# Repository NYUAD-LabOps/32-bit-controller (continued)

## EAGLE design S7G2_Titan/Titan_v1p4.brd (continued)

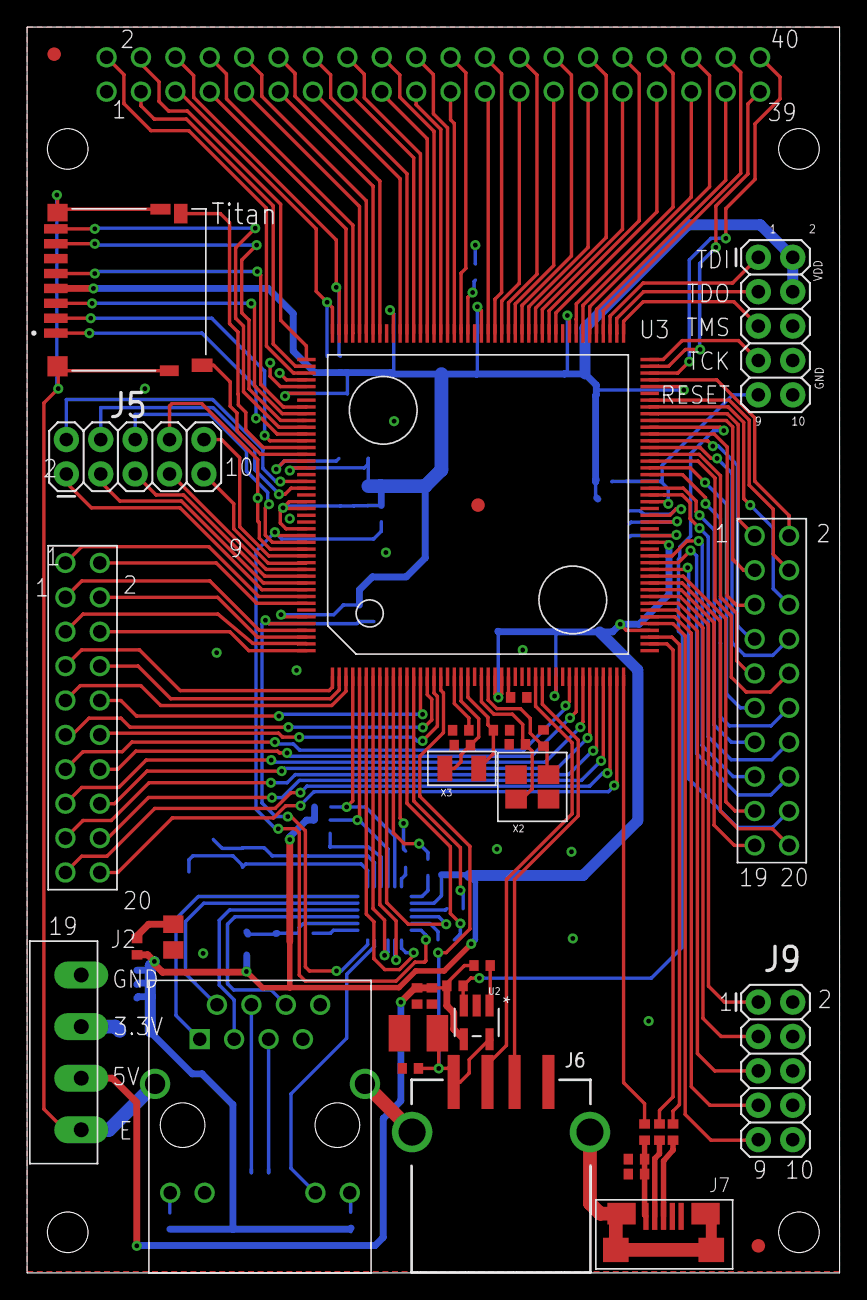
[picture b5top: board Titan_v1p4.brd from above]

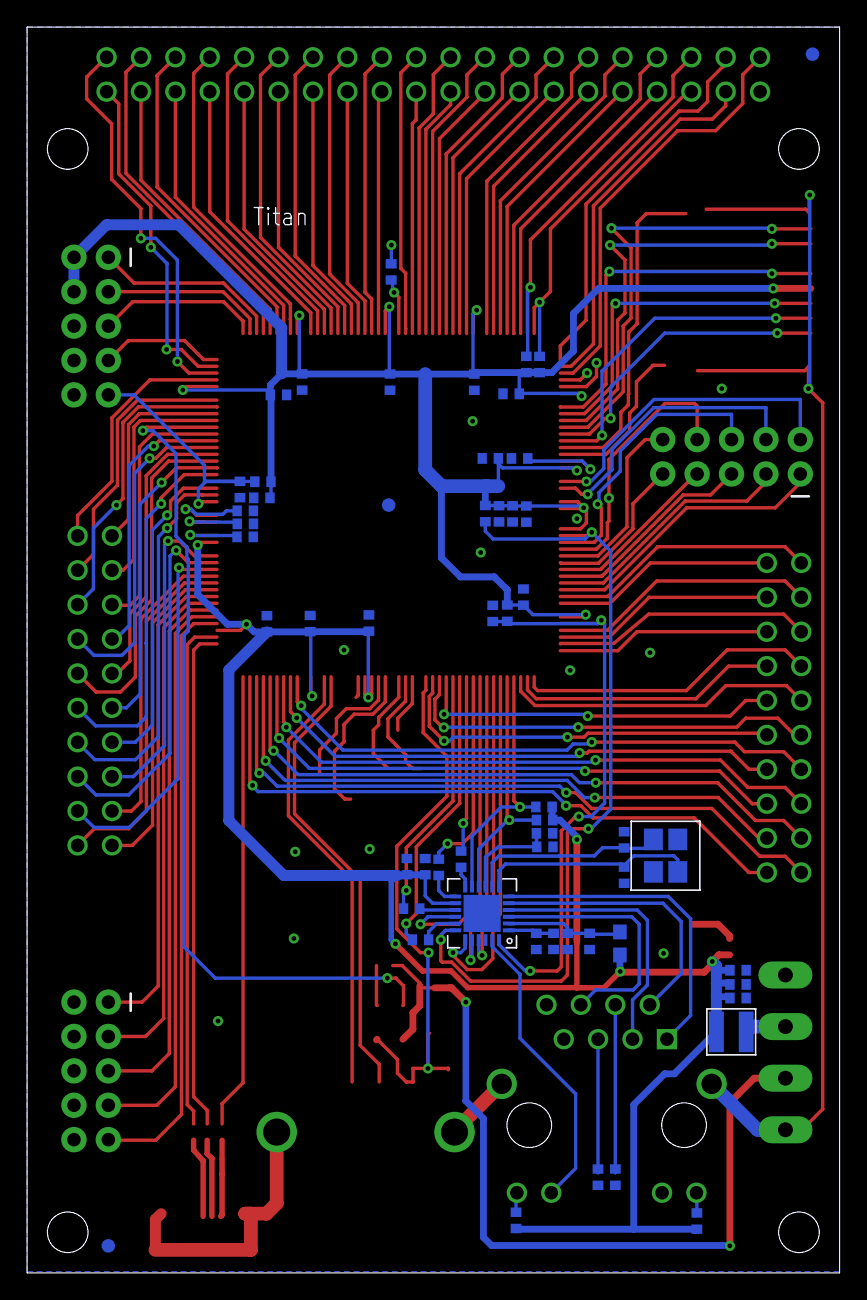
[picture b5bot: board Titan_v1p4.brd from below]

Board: 2 copper layers, 60.0 x 92.0 mm, 93 parts (56 on the bottom side), 165 nets.
